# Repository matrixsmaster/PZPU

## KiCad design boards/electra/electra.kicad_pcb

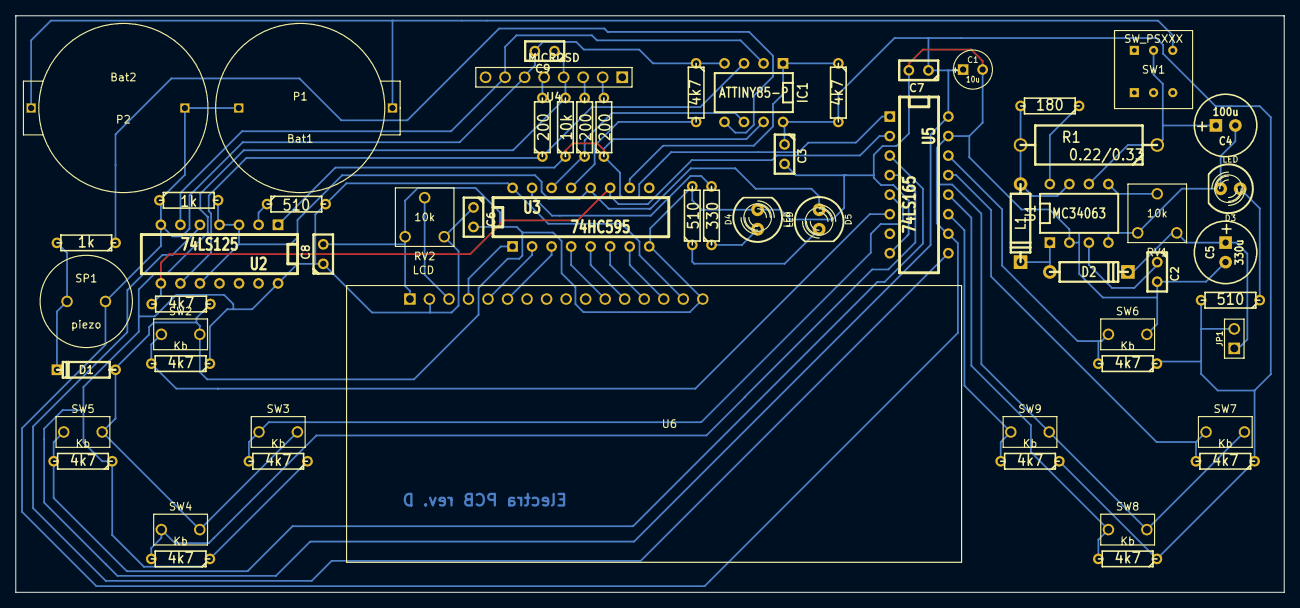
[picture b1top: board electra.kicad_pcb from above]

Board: 2 copper layers, 165.0 x 75.0 mm, 60 parts (0 on the bottom side), 45 nets.

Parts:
C1: 10u; C1V5
C2: 1500p; C1
C3: 100n; C1
C4: 100u; C1V8
C5: 330u; C1V8
C6: 150n; C1
C7: 330n; C1
C8, C9: 680n; C1
D1: BAT42; D3
D2: 1N5819; D4
D3, D4, D5: LED; LED-5MM
IC1: ATTINY85-P; DIP-8__300
JP1: JUMPER; PIN_ARRAY_2X1
L1: 170/220 uH; D4
P1: Bat1; CH-224
P2: Bat2; CH-224
R1: 0.22/0.33; R7
R2, R13: 1k; R3
R3: 180; R3
R4, R8, R23: 510; R3
R5, R6, R14, R15, R16, R17, R18, R19, R20, R21, R22: 4k7; R3
R7: 10k; R3
R9, R10, R11: 200; R3
R12: 330; R3
RV1, RV2: 10k; RVB1
SP1: piezo; buzzer_PKM13
SW1: SW_PSXXX; Butt_B170
SW2, SW3, SW4, SW5, SW6, SW7, SW8, SW9: Kb; butt_TC-3120
U1: MC34063; DIP-8__300
U2: 74LS125; DIP-14__300
U3: 74HC595; DIP-16__300
U4: MICROSD; pin_array_8x1
U5: 74LS165; DIP-16__300
U6: LCD; LCD1602

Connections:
+3.3V: C1.1, C3.1, C6.1, C7.1, C8.1, C9.1, IC1.8, JP1.2, R4.2, R5.2, R7.2, R8.2, R14.1, R15.1, R16.1, R17.1, R18.1, R19.1, R20.1, R21.1, RV2.3, U2.14, U3.16, U4.4, U5.16, U6.2, U6.15
GND: C1.2, C2.2, C3.2, C4.2, C5.2, C6.2, C7.2, C8.2, C9.2, D1.1, D3.2, D4.2, IC1.4, P1.2, P2.2, R6.1, R13.1, R22.1, R23.2, RV1.1, RV2.1, SP1.2, SW2.2, SW3.2, SW4.2, SW5.2, SW6.2, SW7.2, SW8.2, SW9.2, U1.2, U1.4, U2.7, U3.8, U4.6, U5.8, U5.10, U5.15, U6.1, U6.16
unnamed: R6.2, U3.13
unnamed: IC1.6, R10.1, U3.14
unnamed: D4.1, R12.1
unnamed: U3.7, U6.14
unnamed: R12.2, U3.15
unnamed: R11.2, U4.5
unnamed: R10.2, U4.3
unnamed: R9.2, U4.2
unnamed: U3.1, U6.4
unnamed: U3.2, U6.5
unnamed: U3.3, U6.6
unnamed: U3.4, U6.11
unnamed: U3.5, U6.12
unnamed: U3.6, U6.13
unnamed: U2.5, U5.9
unnamed: R22.2, U2.8, U3.11, U5.2
unnamed: D5.2, R23.1
unnamed: D1.2, R2.2, SP1.1
unnamed: D3.1, R4.1
unnamed: R8.1, U2.2
unnamed: L1.1, R1.2, R3.2, U1.7
unnamed: C2.1, U1.3
unnamed: C5.1, D2.2, JP1.1, RV1.3
unnamed: RV1.2, U1.5
unnamed: IC1.3, R11.1, U2.9
unnamed: IC1.7, R7.1, R9.1, U2.1, U5.1
unnamed: IC1.2, U2.6, U4.7
unnamed: IC1.1, R5.1, U3.10
unnamed: IC1.5, R2.1
unnamed: RV2.2, U6.3
unnamed: R21.2, SW9.1, U5.11
unnamed: R20.2, SW8.1, U5.12
unnamed: R19.2, SW7.1, U5.13
unnamed: R18.2, SW6.1, U5.14
unnamed: P1.1, P2.1, SW1.2
unnamed: R3.1, U1.8
unnamed: D2.1, L1.2, U1.1
unnamed: R14.2, SW2.1, U5.6
unnamed: R15.2, SW3.1, U5.5
unnamed: R16.2, SW4.1, U5.4
unnamed: R17.2, SW5.1, U5.3
unnamed: D5.1, R13.2, U2.3, U2.4, U2.10, U3.12
VDD: C4.1, R1.1, SW1.3, U1.6

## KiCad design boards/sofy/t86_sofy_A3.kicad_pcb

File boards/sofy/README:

This particular board was created using old KiCad (2013) with many deeply fragmentated libraries. So I'll release only schematics and PCBs, without cmp or pro files, but with libraries necessary to correctly render the schematics. You can just open sch file in eeschema, connect lib files and see the final product.
Since pcbnew embedding footprints into pcb file, there's no need for any additional mod files.

Next projects will be complete thanks to github-enhanced CvPcb in a new KiCad 4.

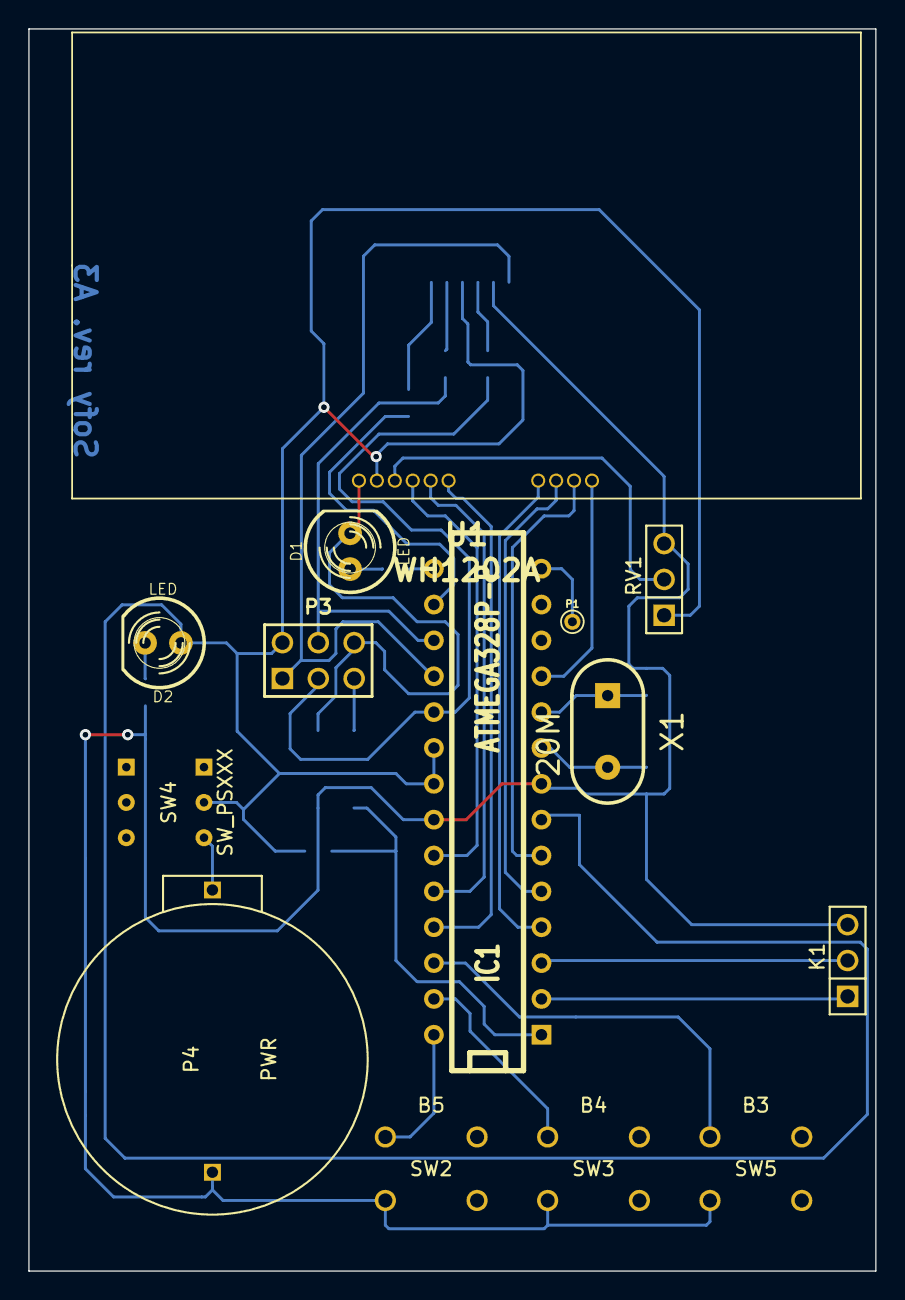
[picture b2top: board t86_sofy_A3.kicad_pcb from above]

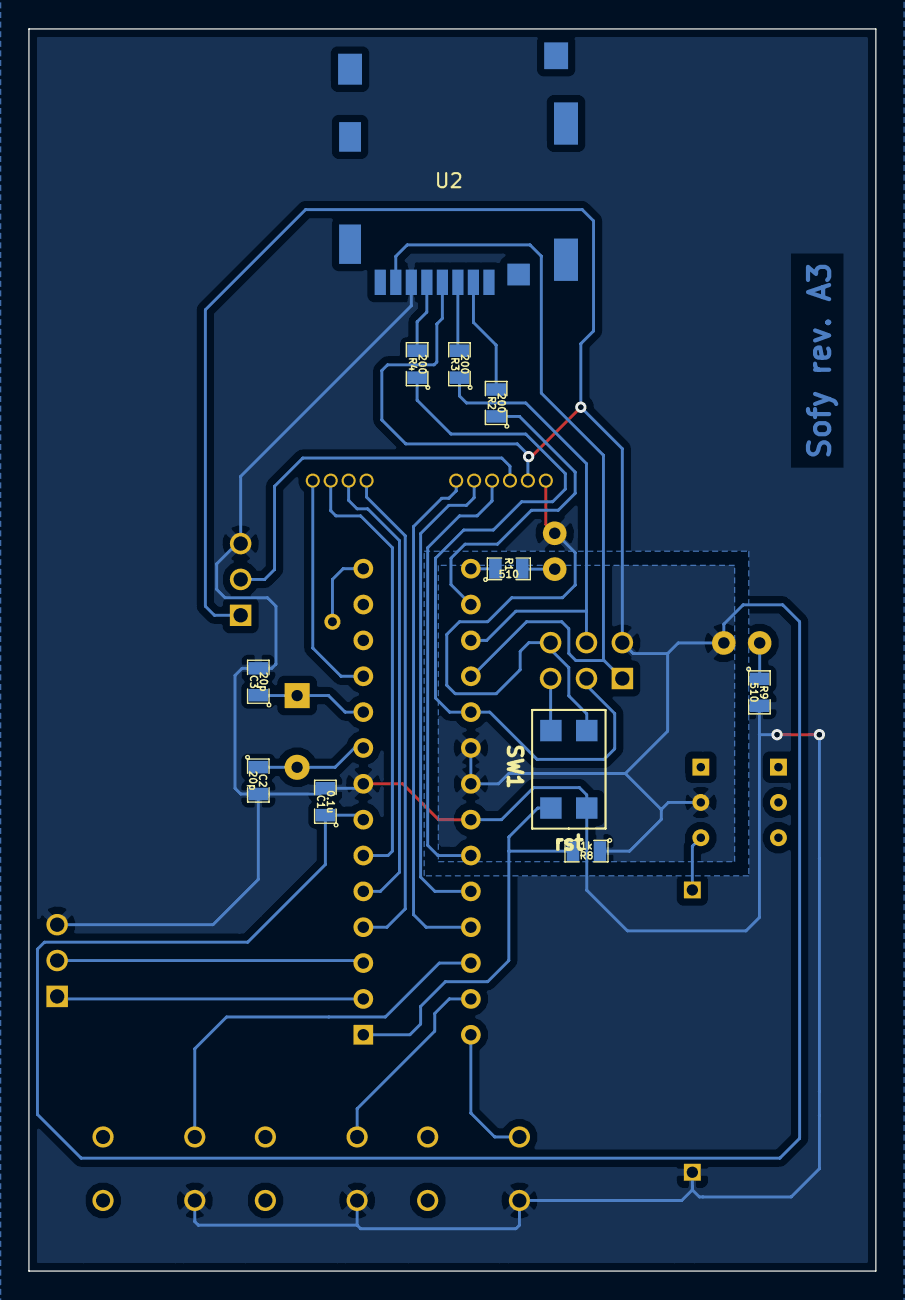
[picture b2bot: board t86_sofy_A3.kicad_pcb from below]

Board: 2 copper layers, 60.0 x 88.0 mm, 25 parts (11 on the bottom side), 30 nets.

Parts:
C1: 0.1u; SM0805
C2, C3: 20p; SM0805
D1, D2: LED; LED-5MM
IC1: ATMEGA328P-P; DIP-28__300
K1: UART; PIN_ARRAY_3X1
P1: CONN_1; PINTST
P3: ICSP; pin_array_3x2
P4: PWR; CH-224
R1, R9: 510; SM0805
R2, R3, R4: 200; SM0805
R8: 1k; SM0805
RV1: 2k; PIN_ARRAY_3X1
SW1: rst; but_7914G
SW2: B5; Butt_06xx
SW3: B4; Butt_06xx
SW4: SW_PSXXX; Butt_B170
SW5: B3; Butt_06xx
U1: WH1202A; OLED DISPLAY
U2: MICROSD; microSD
X1: 20M; VALVE-GLIMM

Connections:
GND: C1.2, C2.2, C3.2, D1.2, IC1.8, IC1.22, K1.3, P3.6, P4.2, R9.2, RV1.3, SW1.2, SW2.2, SW3.2, SW5.2, U1.1, U2.6
unnamed: IC1.2, K1.1
unnamed: IC1.1, P3.5, R8.2, SW1.1
unnamed: C2.1, IC1.9, X1.2
unnamed: IC1.3, K1.2
unnamed: IC1.24, U1.5
unnamed: IC1.5, U1.12
unnamed: IC1.4, U1.11
unnamed: IC1.25, U1.6
unnamed: IC1.23, U1.4
unnamed: IC1.16, R2.1
unnamed: IC1.18, P3.1, U2.7
unnamed: IC1.19, P3.3, R4.1
unnamed: IC1.15, R1.1
unnamed: IC1.17, P3.4, R3.1
unnamed: IC1.14, P1.1
unnamed: P4.1, SW4.2
unnamed: RV1.2, U1.3
unnamed: D2.2, R9.1
unnamed: IC1.11, U1.14
unnamed: IC1.6, U1.13
unnamed: IC1.26, SW5.1
unnamed: IC1.27, SW3.1
unnamed: IC1.28, SW2.1
unnamed: D1.1, R1.2
unnamed: R4.2, U2.5
unnamed: R3.2, U2.3
unnamed: C3.1, IC1.10, X1.1
unnamed: R2.2, U2.2
VCC: C1.1, D2.1, IC1.7, IC1.20, IC1.21, P3.2, R8.1, RV1.1, SW4.3, U1.2, U2.4

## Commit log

2015-12-24 Added testbench for manual memory management code.
2015-12-27 Added managed RAM test, test failed
2015-12-27 Before RAMptr impl.
2015-12-28 Next step toward managed external memory.
2016-01-02 The last attempt to inject external memory kludge
2016-01-02 Finally, I gave up with MRAM, thanks to CAST macro
2016-01-03 Instructions lookup table made static, DAA_DAS instructions bug fixed
2016-03-03 t86 experiment updated
2016-03-03 First successfull compilation for zpu-elf
2016-03-03 Some emulated IO added, still untested
2016-03-03 Dumb RTC tested
2016-03-03 USRIO tested
2016-03-06 Added ZPU testing programs
2016-03-06 Added IO stub, fixed loadSP, storeSP, emulate instructions
2016-03-06 First trace more or less equal to gdb disassembler output with zpusim
2016-03-07 PZPU seems to read UART data
2016-03-07 PZPU Hello world program emulated successfully
2016-03-07 PZPU UART Rx working
2016-03-07 Added PZPU internal cycles counter IO
2016-03-07 Interface added for PZPU frequency request
2016-03-07 Debug messages model changed
2016-03-07 PZPU: going towards makefile model
2016-03-07 Makefiles added for PC and AVR targets
2016-03-07 AVR target updated
2016-03-07 Added SD card reader library for AVR-based PZPU
2016-03-08 AVR port updated
2016-03-09 Changed ram_init() iface, fixed AVR UART baudrate bug
2016-03-09 RAM init code for AVR updated
2016-03-09 Debugging in progress (DNU)
2016-03-10 Byte ordering bug fixed, additional debug messages for RAM added, one step towards format unification, first runs log files appended
2016-03-10 Second swap() version
2016-03-10 Third swap() version
2016-03-10 Removed redundant code
2016-03-10 Quick and dirty image creator tool implemented and tested
2016-03-11 Added LCD output feature for PZPU AVR port
2016-03-13 Instructions cache implemented
2016-03-13 Stack cache implemented
2016-03-13 Caching ported to AVR host. First test is positive
2016-03-13 Light fixes to AVR port UI
2016-03-13 Fixed SCache init debug output
2016-03-13 Updated for size tuning
2016-03-17 Added Sofy board rev.A0
2016-03-17 Configuration layout slightly changed, fixed pin mapping for Sofy-A0 board with 25MHz overclock. SPI transfer switched from double-speed to normal speed in order to stabilize line.
2016-03-17 Image creator updated
2016-03-17 Image creator random offset generation bug fixed
2016-03-19 Added Sofy board rev. A3. Board manufactured and successfully tested.
2016-03-19 Fixed size testing bug
2016-03-22 Last changes before rearrangement of PZPU virtual peripherals. Imgcrt temporarily broken.
2016-03-22 PZPU code prepared to use with other embedded platforms.
2016-03-26 Changes in the source tree tested on real Sofy rev.A0
2016-03-26 More changes in code modules layout for different hardware ports
2016-03-26 Another changes in tree structure. Tested.
2016-03-26 Utils module added for AVR ports. Tested.
2016-03-26 First successful, yet defunct, compilation for Electra board target (tiny85)
2016-03-27 AVR tiny port of PZPU seems to be ready to receive its first image
2016-03-27 Imgcrt: added arguments parsing and additional checks with helpful messaging.
2016-03-28 Both AVR ports is now working. Imgcrt updated.
2016-03-28 Small fixes and improvements for both mega and tiny ports. Cache for tiny is now working.
2016-03-30 Implemented high-speed hack to make SPI transactions of SD sectors much faster. Tested for read operation.
2016-03-30 Implemented high-speed hack for sector write transactions.
2016-03-30 Last fixes and tunings for ATTiny port.
2016-03-30 Electra board changed.
2016-04-01 Repository moved from doscard/tiny86-avr branch. Now it's completely separated repo.
2016-04-01 PCB file added for Electra board
2016-04-01 Electra PCB optimized.
2016-04-13 Added ramfile virtual RAM option.
2016-04-13 Ramfile tested with caching.
2016-04-15 Initial preparations are done for Parallax Propeller 1 port.
2016-04-16 PZPU successfully ran on p8x32a demoboard
2016-04-17 Propeller makefile fixed for current stable PropGCC release.
2016-04-17 Master branch clean. Propeller port now in its own branch until it'll be ready.
2016-04-17 Successfully tested on demoboard with two separate SD cards. SDXMMC (firmware) card on P0-P3, PZPU (prog and virtual RAM) on P4-P7. O2. Still very slow.
2018-05-11 Added 'No Card' exception
2019-06-30 Boards: added PDF versions of design documents
2019-08-26 Added QZPU test project
2019-08-26 Started a move towards OISC CPU
2019-08-26 OISC CPU port: all bitwise operations are wrapped
2019-08-26 OISC CPU port: added working HSQ version
2019-08-26 OISC CPU port: added missing header
2019-08-26 OISC CPU port: added simple Subleq interpreter
2019-08-26 Subleq: added faster implementation
2019-08-26 Subleq: WIP. Debugging HSQZPU.
2019-08-27 Subleq: first sanity test passed
2019-08-27 Subleq: WIP on running F86
